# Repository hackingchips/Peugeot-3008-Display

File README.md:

## Repairing Peugeot 3008 display. ##

This repository is about changing the LCD crystal of my Peugeot 3008 multifunction display.

If you want more information go the following links:

* http://www.hackingchips.com/2020/09/reparacion-de-display-peugeot-3008.html
* http://www.hackingchips.com/2020/09/reparacion-de-display-peugeot-3008_22.html
* http://www.hackingchips.com/2020/09/reparacion-de-display-peugeot-3008_23.html
* http://www.hackingchips.com/2020/09/reparacion-de-display-peugeot-3008_25.html
* http://www.hackingchips.com/2020/09/reparacion-de-display-peugeot-3008_26.html
* http://www.hackingchips.com/2020/10/reparacion-de-display-peugeot-3008.html

### Repository. ###
* Docs: Datasheets and notes.
* Firmware/PeugeotDisplay4245: Firmware for Cypress PSoC CY8C4245 (PSoC Creator 4.3 project).
* Hardware/PeugeotTypeCDisplayHack: Kicad project (schematic & pcb board).
* Mechanical: 3D models.
* NewestArchives_xxx_date_xxx: Latest binary & docs.

#### Thanks to Peter Pinter ([morcibacsi]). His project PSAWifiDisplayControl (https://github.com/morcibacsi/PSAWifiDisplayControl) saved me a lot of work. ####

[morcibacsi]: https://github.com/morcibacsi

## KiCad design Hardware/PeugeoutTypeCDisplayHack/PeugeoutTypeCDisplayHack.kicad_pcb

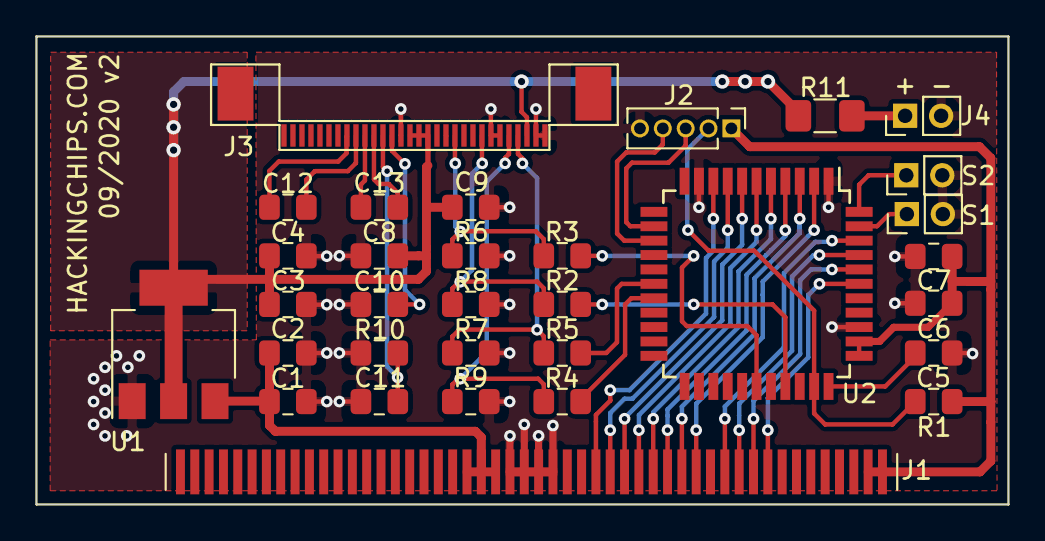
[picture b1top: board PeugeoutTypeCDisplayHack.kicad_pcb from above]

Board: 2 copper layers, 54.0 x 26.0 mm, 32 parts (0 on the bottom side), 36 nets.

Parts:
C1, C3, C8: 10uF; C_0805_2012Metric_Pad1.15x1.40mm_HandSolder
C2: 100nf; C_0805_2012Metric_Pad1.15x1.40mm_HandSolder
C4, C7, C9, C10, C11: 100nF; C_0805_2012Metric_Pad1.15x1.40mm_HandSolder
C5: 1uF/25; C_0805_2012Metric_Pad1.15x1.40mm_HandSolder
C6: 10nF; C_0805_2012Metric_Pad1.15x1.40mm_HandSolder
C12, C13: 4u7; C_0805_2012Metric_Pad1.15x1.40mm_HandSolder
J1: PeugeotPCBConnector
J2: Conn_01x05; PinHeader_1x05_P1.27mm_Vertical
J3: ER-CON30HB-1
J4: Backlight; PinHeader_1x02_P2.00mm_Vertical
R1: 4K7; R_0805_2012Metric_Pad1.15x1.40mm_HandSolder
R2, R3, R4, R5: 1K; R_0805_2012Metric_Pad1.15x1.40mm_HandSolder
R6, R7, R8, R9: 2K; R_0805_2012Metric_Pad1.15x1.40mm_HandSolder
R10: 10M; R_0805_2012Metric_Pad1.15x1.40mm_HandSolder
R11: ???; R_1206_3216Metric_Pad1.42x1.75mm_HandSolder
S1, S2: F.Use; PinHeader_1x02_P2.00mm_Vertical
U1: LM1117-3.3; SOT-223-3_TabPin2
U2: CY8C4245AXI-483; TQFP-44_10x10mm_P0.8mm

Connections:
+3V3: C3.1, C4.1, C8.1, C9.1, J3.15, J3.16, J3.17, J3.28, R11.2, U1.2
+5V: C1.1, C2.1, C6.1, C7.1, J1.1, J1.2, J1.28, J1.29, J1.30, J2.1, R1.1, U1.3, U2.34, U2.35
/-RESET: J1.10, U2.40
/-XRES: J2.2, R1.2, U2.32
/A0: J1.11, U2.41
/CS: J1.9, U2.39
/D0: J1.14, U2.2
/D1: J1.15, U2.3
/D2: J1.16, U2.4
/D3: J1.17, U2.5
/D4: J1.18, U2.6
/D5: J1.19, U2.7
/D6: J1.20, U2.8
/D7: J1.21, U2.9
/E: J1.12, U2.42
/F1: S1.1, U2.43
/F2: S2.1, U2.44
/LCD_CD: J3.26, R4.1, R9.1
/LCD_RESET: J3.27, R5.1, R7.1
/LCD_SCK: J3.23, R2.1, R8.1
/LCD_SDA: J3.20, R3.1, R6.1
/VBIAS: C10.1, J3.13
GND: C1.2, C2.2, C3.2, C4.2, C5.2, C6.2, C7.2, C8.2, C9.2, C10.2, C11.2, J1.24, J1.25, J1.26, J1.27, J2.5, J3.14, J3.24, J3.25, J3.29, J3.30, J4.2, R6.2, R7.2, R8.2, R9.2, R10.2, S1.2, S2.2, U1.1, U2.1, U2.10, U2.36
unnamed: C5.1, U2.33
unnamed: C11.1, J3.12, R10.1
unnamed: C12.1, J3.9
unnamed: C12.2, J3.8
unnamed: C13.1, J3.11
unnamed: C13.2, J3.10
unnamed: J2.3, U2.13
unnamed: J2.4, U2.14
unnamed: J4.1, R11.1
unnamed: R2.2, U2.30
unnamed: R3.2, U2.28
unnamed: R4.2, U2.18
unnamed: R5.2, U2.17

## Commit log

2020-10-22 Added readme.me
2021-03-20 Update README.md
    Fixed typo and added link :)
